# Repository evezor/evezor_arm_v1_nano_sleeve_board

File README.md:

# evezor_arm_v1_nano_sleeve_board

This board was intended to sit at the elbow of the robotic arm and its primary function was to obtain and smooth readings from the encoders and to drive the neopixel arrays at each joint. 

It also featured 2 ide ports that followed the Gadgeteer standard which I found to be a less than satisfactory attempt at creating modular systems. More on these reasonings can be found in some of my other posts.

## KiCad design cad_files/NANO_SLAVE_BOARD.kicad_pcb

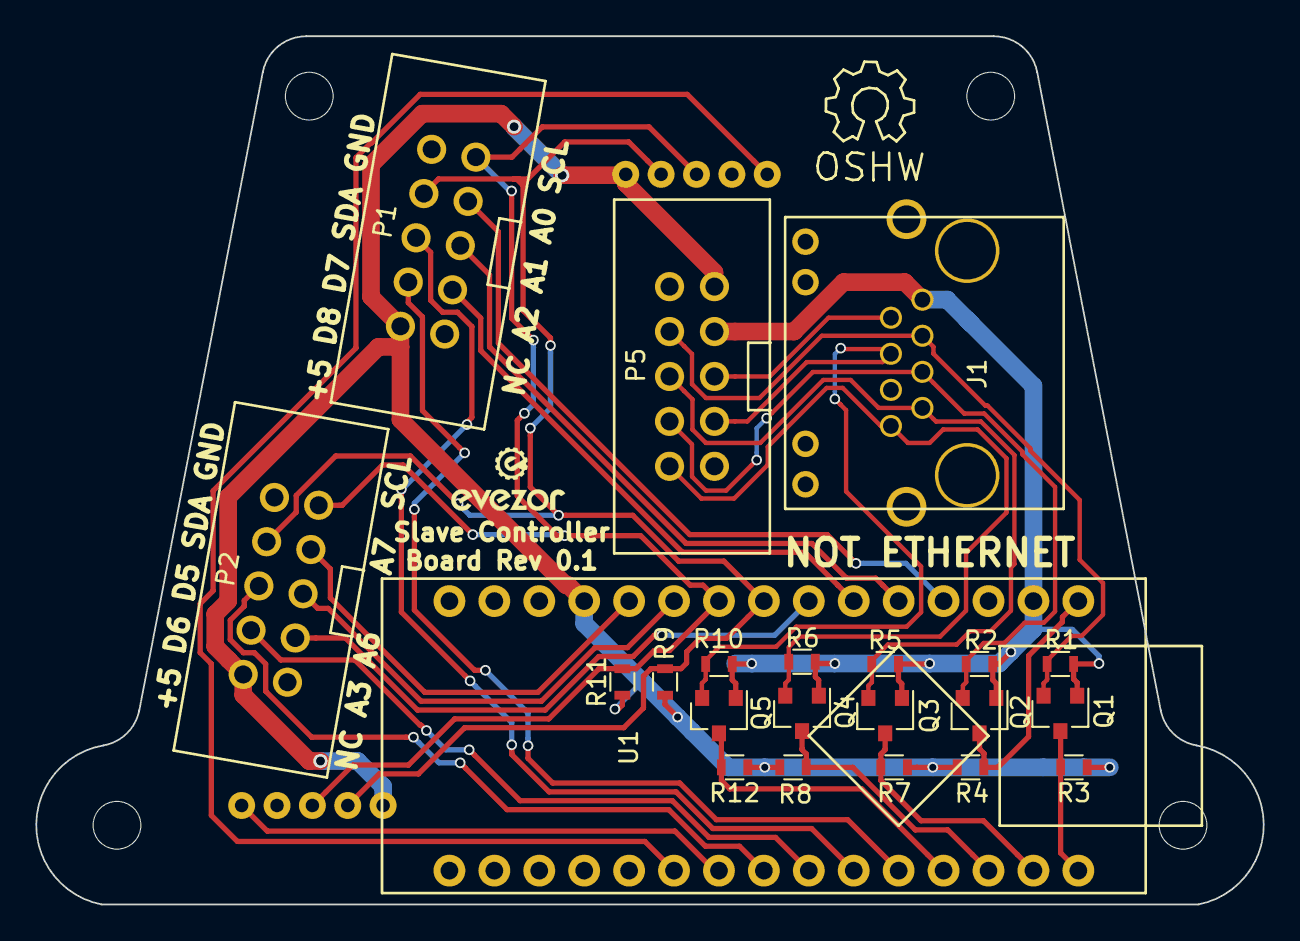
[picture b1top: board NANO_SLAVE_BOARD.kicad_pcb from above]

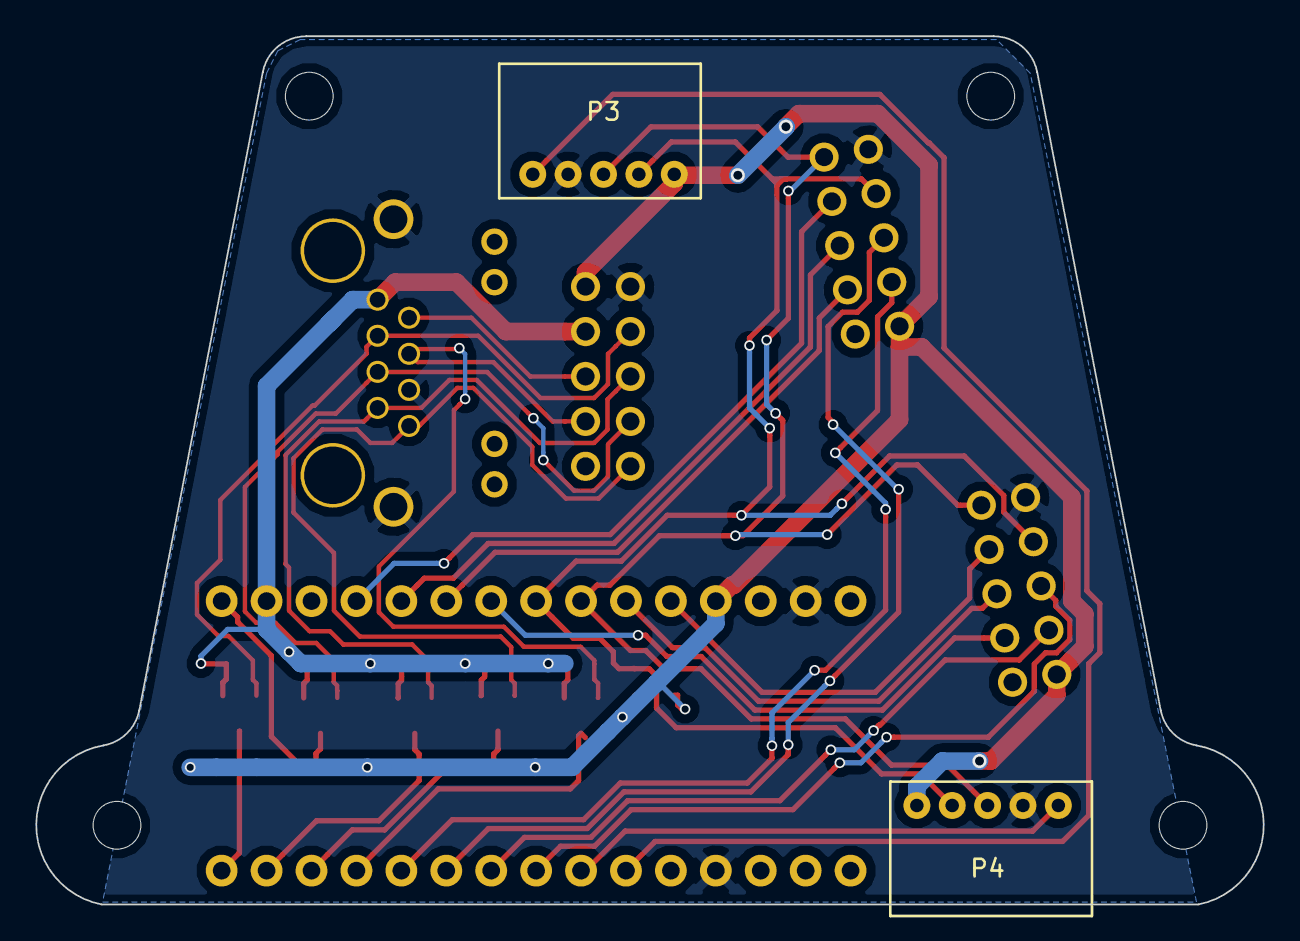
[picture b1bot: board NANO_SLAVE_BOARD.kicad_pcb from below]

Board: 2 copper layers, 69.4 x 49.1 mm, 24 parts (2 on the bottom side), 28 nets.

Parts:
J1: RJ45_SHIELDED
P1, P2, P5: CONN_02X05; 10_PIN_IDC
P3, P4: CONN_01X05; S5B-PH-K-S(LF)(SN)
Q1, Q2, Q3, Q4, Q5: BSS138; SOT-23
R1, R2, R3, R4, R5, R6, R7, R8, R10, R12: 10K; R_0603
R9, R11: 4.7K; R_0603
U1: arduino_nano; ARDUINO_NANO

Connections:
+3V3: J1.1, P5.7, Q1.1, Q2.1, Q3.1, Q4.1, Q5.1, R1.1, R2.1, R5.1, R6.1, R10.1, U1.2
+5V: P1.2, P2.2, P3.1, P4.1, P5.9, R3.1, R4.1, R7.1, R8.1, R9.1, R11.1, R12.1, U1.12
A0: P1.7, U1.4
A1: P1.5, U1.5
A2: P1.3, U1.6
A3: P2.3, U1.7
A6: P2.5, U1.10
A7: P2.7, U1.11
D3: P3.5, U1.21
D4: P4.5, U1.22
D5: P2.6, U1.23
D6: P2.4, U1.24
D7: P1.6, U1.25
D8: P1.4, U1.26
D9: Q5.3, R12.2, U1.27
GND: J1.7, J1.13, P1.10, P2.10, P3.4, P4.4, P5.10, U1.14, U1.19
MISO: Q1.3, R3.2, U1.30
MOSI: Q3.3, R7.2, U1.29
SCK: Q2.3, R4.2, U1.1
SCL: P1.9, P2.9, P3.3, P4.3, R11.2, U1.9
SDA: P1.8, P2.8, P3.2, P4.2, R9.2, U1.8
SS: Q4.3, R8.2, U1.28
S_CS: J1.8, P5.2, Q4.2, R6.2
S_MISO: J1.2, P5.8, Q1.2, R1.2
S_MOSI: J1.4, P5.6, Q3.2, R5.2
S_Q6: J1.6, P5.3, Q5.2, R10.2
S_Q8: J1.5, P5.5
S_SCK: J1.3, P5.4, Q2.2, R2.2

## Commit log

2023-09-20 init
